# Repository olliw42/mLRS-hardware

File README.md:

# mLRS Hardware #

Repository for some mLRS hardware design files.

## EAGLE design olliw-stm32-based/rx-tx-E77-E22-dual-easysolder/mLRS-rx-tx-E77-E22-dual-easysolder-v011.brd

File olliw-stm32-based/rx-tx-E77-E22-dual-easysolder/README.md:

# mLRS Hardware: Easy-To-Solder Board E77 E22 dual #

For the through-hole parts, Mouser parts numbers are listed in the electric scheme. A list of parts is also available here https://www.mouser.de/ProjectManager/ProjectDetail.aspx?AccessID=b60c19cf3a.

These are of course only suggestions, these and equally suitable parts can be sourced from many places.

The EByte E77-900M22S module is relatively new. It can be ordered from the "EBYTE Official Store" on AliExpress.

The EByte E22-900M22S module is around for some while and can be ordered on AliExpress from several sources (the "EBYTE Official Store" may not be the cheapest offer).

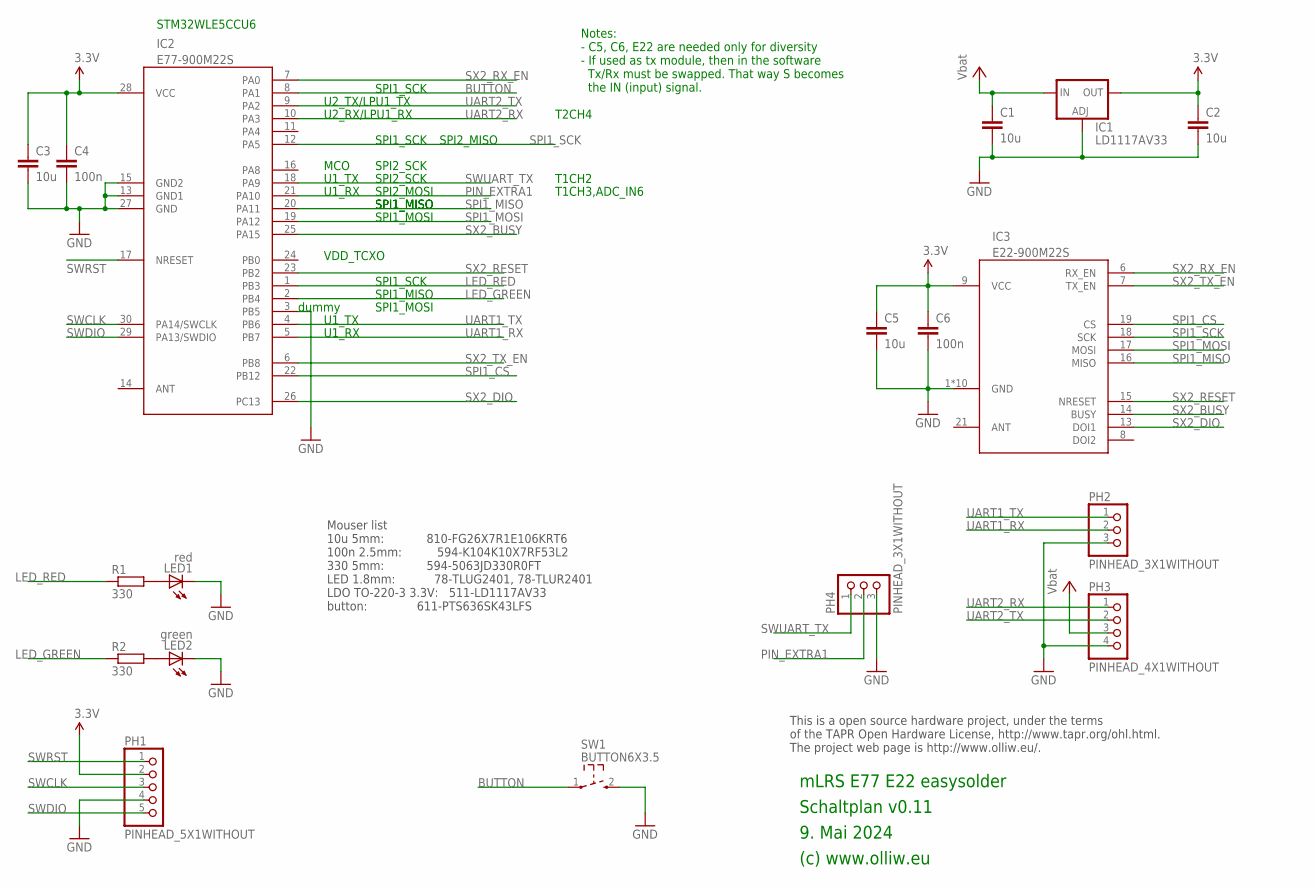
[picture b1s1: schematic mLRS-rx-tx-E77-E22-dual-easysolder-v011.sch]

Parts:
C1, C2: 10u; C050-045X075
C3, C5: 10u; C050-024X044
C4, C6: 100n; C025-024X044
IC1: LD1117AV33; TO220L1
IC2: E77-900M22S
IC3: E22-900M22S
LED1: red; LED1.8MM
LED2: green; LED1.8MM
PH1: PINHEAD_5X1WITHOUT; PINHEAD_5X1_WO
PH2, PH4: PINHEAD_3X1WITHOUT; PINHEAD_3X1_WO
PH3: PINHEAD_4X1WITHOUT; PINHEAD_4X1_WO
R1, R2: 330; R0204/6.25
SW1: BUTTON6X3.5; BUTTON-THT

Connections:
3.3V: C2.1, C3.1, C4.1, C5.1, C6.1, IC1.2 (OUT), IC2.28 (VCC), IC3.9 (VCC), PH1.2
BUTTON: IC2.8 (PA1), SW1.1
GND: C1.2, C2.2, C3.2, C4.2, C5.2, C6.2, IC1.1 (ADJ), IC2.3 (PB5), IC2.13 (GND1), IC2.15 (GND2), IC2.27 (GND), IC3.1 (GND), IC3.2 (GND), IC3.3 (GND), IC3.4 (GND), IC3.5 (GND), IC3.10 (GND), IC3.11 (GND), IC3.12 (GND), IC3.20 (GND), IC3.22 (GND), LED1.K (C), LED2.K (C), PH1.4, PH2.3 (5), PH3.4, PH4.3 (5), SW1.2 (3)
LED_GREEN: IC2.2 (PB4), R2.1
LED_RED: IC2.1 (PB3), R1.1
unnamed: LED1.A, R1.2
unnamed: LED2.A, R2.2
PIN_EXTRA1: IC2.21 (PA10), PH4.2 (3)
SPI1_CS: IC2.22 (PB12), IC3.19 (CS)
SPI1_MISO: IC2.20 (PA11), IC3.16 (MISO)
SPI1_MOSI: IC2.19 (PA12), IC3.17 (MOSI)
SPI1_SCK: IC2.12 (PA5), IC3.18 (SCK)
SWCLK: IC2.30 (PA14/SWCLK), PH1.3
SWDIO: IC2.29 (PA13/SWDIO), PH1.5
SWRST: IC2.17 (NRESET), PH1.1
SWUART_TX: IC2.18 (PA9), PH4.1
SX2_BUSY: IC2.25 (PA15), IC3.14 (BUSY)
SX2_DIO: IC2.26 (PC13), IC3.13 (DOI1)
SX2_RESET: IC2.23 (PB2), IC3.15 (NRESET)
SX2_RX_EN: IC2.7 (PA0), IC3.6 (RX_EN)
SX2_TX_EN: IC2.6 (PB8), IC3.7 (TX_EN)
UART1_RX: IC2.5 (PB7), PH2.2 (3)
UART1_TX: IC2.4 (PB6), PH2.1
UART2_RX: IC2.10 (PA3), PH3.1
UART2_TX: IC2.9 (PA2), PH3.2
VCC: C1.1, IC1.3 (IN), PH3.3

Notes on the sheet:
9. Mai 2024
(c) www.olliw.eu
mLRS E77 E22 easysolder
Schaltplan v0.11
This is a open source hardware project, under the terms of the TAPR Open Hardware License, http://www.tapr.org/ohl.html. The project web page is http://www.olliw.eu/.
SPI1_SCK
SPI1_MISO
SPI1_MOSI
U1_TX
U1_RX
U2_TX/LPU1_TX
U2_RX/LPU1_RX
SPI2_SCK
VDD_TCXO
SPI2_MOSI
SPI2_MISO
STM32WLE5CCU6
T1CH2
T1CH3,ADC_IN6
Mouser list 10u 5mm: 810-FG26X7R1E106KRT6 100n 2.5mm: 594-K104K10X7RF53L2 330 5mm: 594-5063JD330R0FT LED 1.8mm: 78-TLUG2401, 78-TLUR2401 LDO TO-220-3 3.3V: 511-LD1117AV33 button: 611-PTS636SK43LFS
dummy
T2CH4
Notes: - C5, C6, E22 are needed only for diversity - If used as tx module, then in the software Tx/Rx must be swapped. That way S becomes the IN (input) signal.
MCO

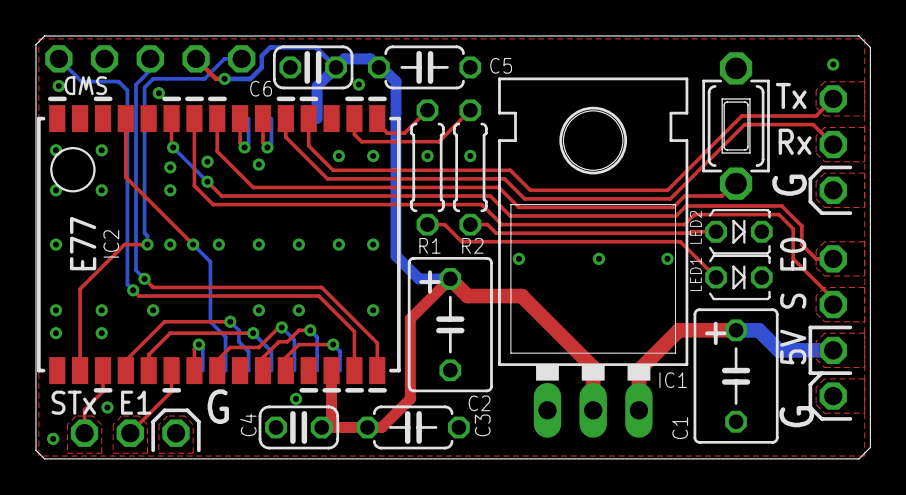
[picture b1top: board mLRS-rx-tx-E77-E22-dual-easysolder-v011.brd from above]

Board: 2 copper layers, 46.4 x 23.5 mm, 18 parts (1 on the bottom side), 26 nets.

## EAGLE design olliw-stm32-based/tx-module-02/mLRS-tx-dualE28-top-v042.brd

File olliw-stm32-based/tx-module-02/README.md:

# ATTENTION #

The v042 designs for the base board, the E22dual board, and the E28dual board are up-to-date.

The v031 dualSx board will not be updated.

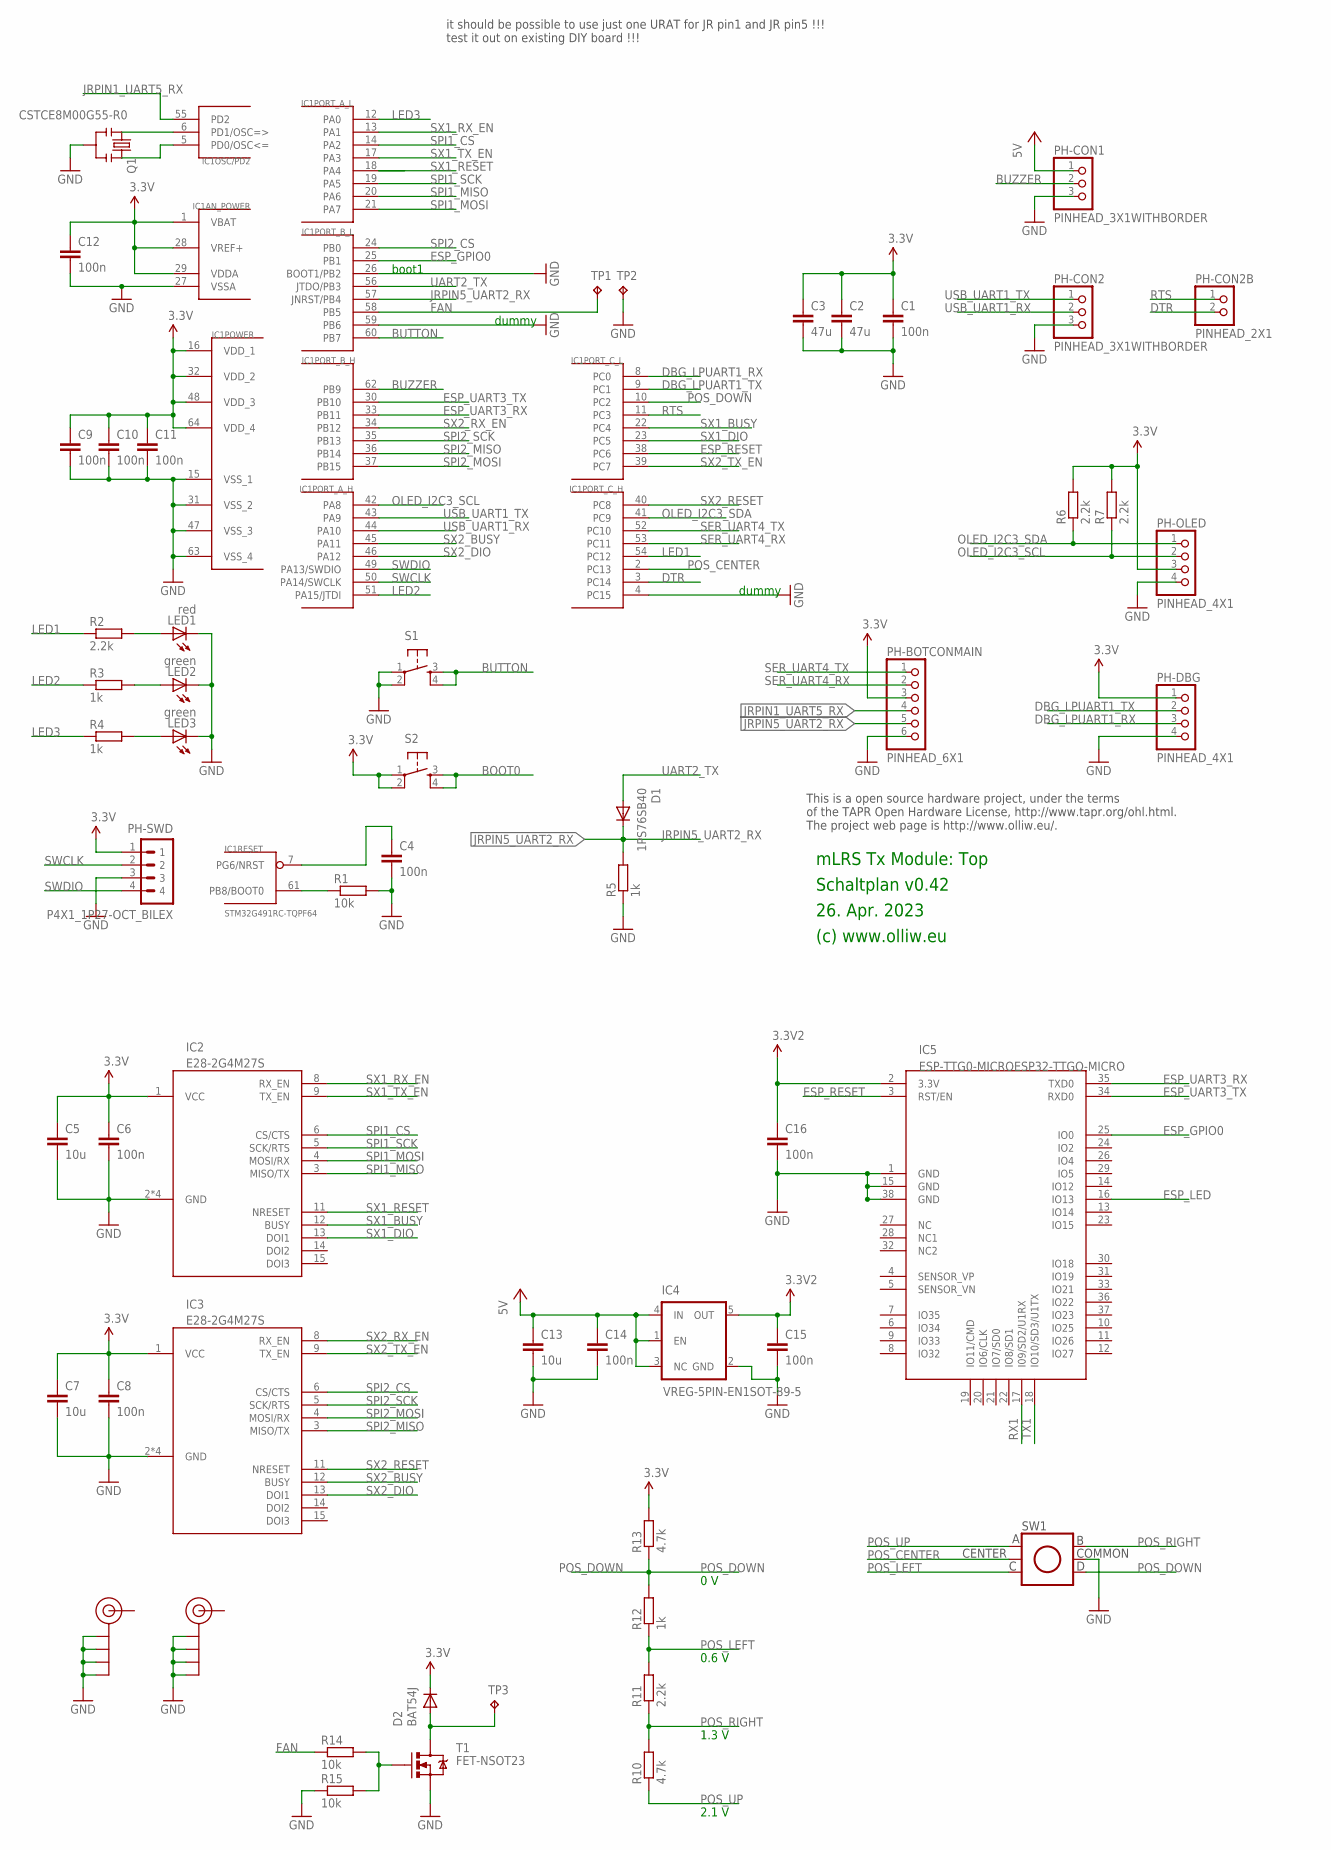
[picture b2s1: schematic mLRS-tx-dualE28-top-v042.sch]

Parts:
C1, C4, C6, C8, C9, C10, C11, C12, C14, C15: 100n; C0402
C2: 47u; C1210
C3: 47u; C1206K
C5, C7, C13: 10u; C0603
C16: 100n; C0603
D1: 1PS76SB40; SOD110-R
D2: BAT54J; SOD110-R
IC1: STM32G491RC-TQPF64; TQFP64
IC2, IC3: E28-2G4M27S; E28-2G4M27
IC4: VREG-5PIN-EN1SOT-89-5; SOT-89-5
IC5: ESP-TTG0-MICROESP32-TTGO-MICRO; ESP32-TTGO-MICRO
LED1: red; CHIPLED_0603
LED2, LED3: green; CHIPLED_0603
PH-BOTCONMAIN: PINHEAD_6X1
PH-CON1, PH-CON2: PINHEAD_3X1WITHBORDER; PINHEAD_3X1
PH-CON2B: PINHEAD_2X1
PH-DBG: PINHEAD_4X1
PH-OLED: PINHEAD_4X1
PH-SWD: P4X1_1P27-OCT_BILEX; 4X1_1P27_OCT_BILEX
Q1: CSTCE8M00G55-R0; RESONATOR-SMD
R1, R14, R15: 10k; R0402
R2, R6, R7, R11: 2.2k; R0402
R3, R4, R5, R12: 1k; R0402
R10, R13: 4.7k; R0402
RF1, RF2: SMA_EDGE; SMA-EDGE
S1, S2: TAC_SWITCHPTH; TACTILE-PTH
SW1: JOYSTICK-5WAY
T1: FET-NSOT23; SOT23
TP1, TP2, TP3: TPB1,27; B1,27

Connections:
2.8V: C15.1, C16.1, IC4.5 (OUT), IC5.2 (3.3V)
3.3V: C1.1, C2.1, C3.1, C5.1, C6.1, C7.1, C8.1, C9.1, C10.1, C11.1, C12.1, D2.C, IC1.1 (VBAT), IC1.16 (VDD_1), IC1.28 (VREF+), IC1.29 (VDDA), IC1.32 (VDD_2), IC1.48 (VDD_3), IC1.64 (VDD_4), IC2.1 (VCC), IC3.1 (VCC), PH-BOTCONMAIN.3, PH-DBG.1, PH-OLED.3, PH-SWD.1, R6.2, R7.2, R13.2, S2.1, S2.2
5V: C13.1, C14.1, IC4.1 (EN), IC4.3 (NC), IC4.4 (IN), PH-CON1.1
BOOT0: IC1.61 (PB8/BOOT0), R1.1, S2.3, S2.4
BUTTON: IC1.60 (PB7), S1.3, S1.4
BUZ-: D2.A, T1.3 (D), TP3.TP
BUZZER: IC1.62 (PB9), PH-CON1.2 (3)
DBG_LPUART1_RX: IC1.8 (PC0), PH-DBG.3
DBG_LPUART1_TX: IC1.9 (PC1), PH-DBG.2
DTR: IC1.3 (PC14), PH-CON2B.2
ESP_GPIO0: IC1.25 (PB1), IC5.25 (IO0)
ESP_LED: IC5.16 (IO13)
ESP_RESET: IC1.38 (PC6), IC5.3 (RST/EN)
ESP_UART3_RX: IC1.33 (PB11), IC5.35 (TXD0)
ESP_UART3_TX: IC1.30 (PB10), IC5.34 (RXD0)
FAN: IC1.58 (PB5), R14.1, TP1.TP
GND: C1.2, C2.2, C3.2, C4.2, C5.2, C6.2, C7.2, C8.2, C9.2, C10.2, C11.2, C12.2, C13.2, C14.2, C15.2, C16.2, IC1.4 (PC15), IC1.15 (VSS_1), IC1.26 (BOOT1/PB2), IC1.27 (VSSA), IC1.31 (VSS_2), IC1.47 (VSS_3), IC1.59 (PB6), IC1.63 (VSS_4), IC2.2 (GND), IC2.7 (GND), IC2.10 (GND), IC2.16 (GND), IC3.2 (GND), IC3.7 (GND), IC3.10 (GND), IC3.16 (GND), IC4.2 (GND), IC5.1 (GND), IC5.15 (GND), IC5.38 (GND), LED1.C, LED2.C, LED3.C, PH-BOTCONMAIN.6, PH-CON1.3 (5), PH-CON2.3 (5), PH-DBG.4, PH-OLED.4, PH-SWD.3, Q1.2, R1.2, R5.1, R15.1, RF1.GND@0 (GND), RF1.GND@1 (GND), RF1.GND@2 (GND), RF1.GND@3 (GND), RF2.GND@0 (GND), RF2.GND@1 (GND), RF2.GND@2 (GND), RF2.GND@3 (GND), S1.1, S1.2, SW1.5 (COMMON), T1.2 (S), TP2.TP
JRPIN1_UART5_RX: IC1.55 (PD2), PH-BOTCONMAIN.4
JRPIN5_UART2_RX: D1.C, IC1.57 (JNRST/PB4), PH-BOTCONMAIN.5, R5.2
LED1: IC1.54 (PC12), R2.1
LED2: IC1.51 (PA15/JTDI), R3.1
LED3: IC1.12 (PA0), R4.1
unnamed: R14.2, R15.2, T1.1 (G)
unnamed: LED1.A, R2.2
unnamed: C4.1, IC1.7 (PG6/NRST)
unnamed: LED2.A, R3.2
unnamed: LED3.A, R4.2
unnamed: IC1.5 (PD0/OSC<=), Q1.3
unnamed: IC1.6 (PD1/OSC=>), Q1.1
OLED_I2C3_SCL: IC1.42 (PA8), PH-OLED.2, R7.1
OLED_I2C3_SDA: IC1.41 (PC9), PH-OLED.1, R6.1
POS_CENTER: IC1.2 (PC13), SW1.2 (CENTER)
POS_DOWN: IC1.10 (PC2), R12.2, R13.1, SW1.6 (D)
POS_LEFT: R11.2, R12.1, SW1.3 (C)
POS_RIGHT: R10.2, R11.1, SW1.4 (B)
POS_UP: R10.1, SW1.1 (A)
RTS: IC1.11 (PC3), PH-CON2B.1
RX1: IC5.17 (I09/SD2/U1RX)
SER_UART4_RX: IC1.53 (PC11), PH-BOTCONMAIN.2
SER_UART4_TX: IC1.52 (PC10), PH-BOTCONMAIN.1
SPI1_CS: IC1.14 (PA2), IC2.6 (CS/CTS)
SPI1_MISO: IC1.20 (PA6), IC2.3 (MISO/TX)
SPI1_MOSI: IC1.21 (PA7), IC2.4 (MOSI/RX)
SPI1_SCK: IC1.19 (PA5), IC2.5 (SCK/RTS)
SPI2_CS: IC1.24 (PB0), IC3.6 (CS/CTS)
SPI2_MISO: IC1.36 (PB14), IC3.3 (MISO/TX)
SPI2_MOSI: IC1.37 (PB15), IC3.4 (MOSI/RX)
SPI2_SCK: IC1.35 (PB13), IC3.5 (SCK/RTS)
SWCLK: IC1.50 (PA14/SWCLK), PH-SWD.2
SWDIO: IC1.49 (PA13/SWDIO), PH-SWD.4
SX1_BUSY: IC1.22 (PC4), IC2.12 (BUSY)
SX1_DIO: IC1.23 (PC5), IC2.13 (DOI1)
SX1_RESET: IC1.18 (PA4), IC2.11 (NRESET)
SX1_RX_EN: IC1.13 (PA1), IC2.8 (RX_EN)
SX1_TX_EN: IC1.17 (PA3), IC2.9 (TX_EN)
SX2_BUSY: IC1.45 (PA11), IC3.12 (BUSY)
SX2_DIO: IC1.46 (PA12), IC3.13 (DOI1)
SX2_RESET: IC1.40 (PC8), IC3.11 (NRESET)
SX2_RX_EN: IC1.34 (PB12), IC3.8 (RX_EN)
SX2_TX_EN: IC1.39 (PC7), IC3.9 (TX_EN)
TX1: IC5.18 (IO10/SD3/U1TX)
UART2_TX: D1.A, IC1.56 (JTDO/PB3)
USB_UART1_RX: IC1.44 (PA10), PH-CON2.2 (3)
USB_UART1_TX: IC1.43 (PA9), PH-CON2.1

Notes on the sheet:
26. Apr. 2023
(c) www.olliw.eu
mLRS Tx Module: Top
Schaltplan v0.42
This is a open source hardware project, under the terms of the TAPR Open Hardware License, http://www.tapr.org/ohl.html. The project web page is http://www.olliw.eu/.
boot1
it should be possible to use just one URAT for JR pin1 and JR pin5 !!! test it out on existing DIY board !!!
0 V
0.6 V
1.3 V
2.1 V
dummy

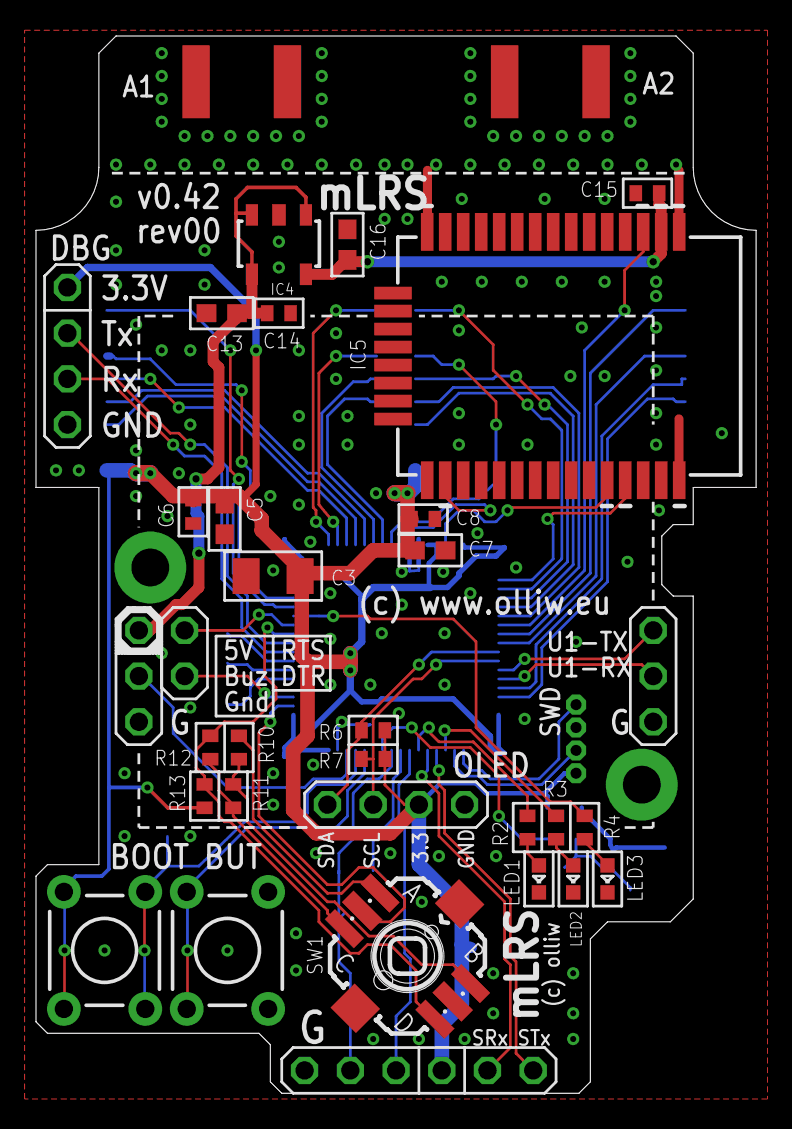
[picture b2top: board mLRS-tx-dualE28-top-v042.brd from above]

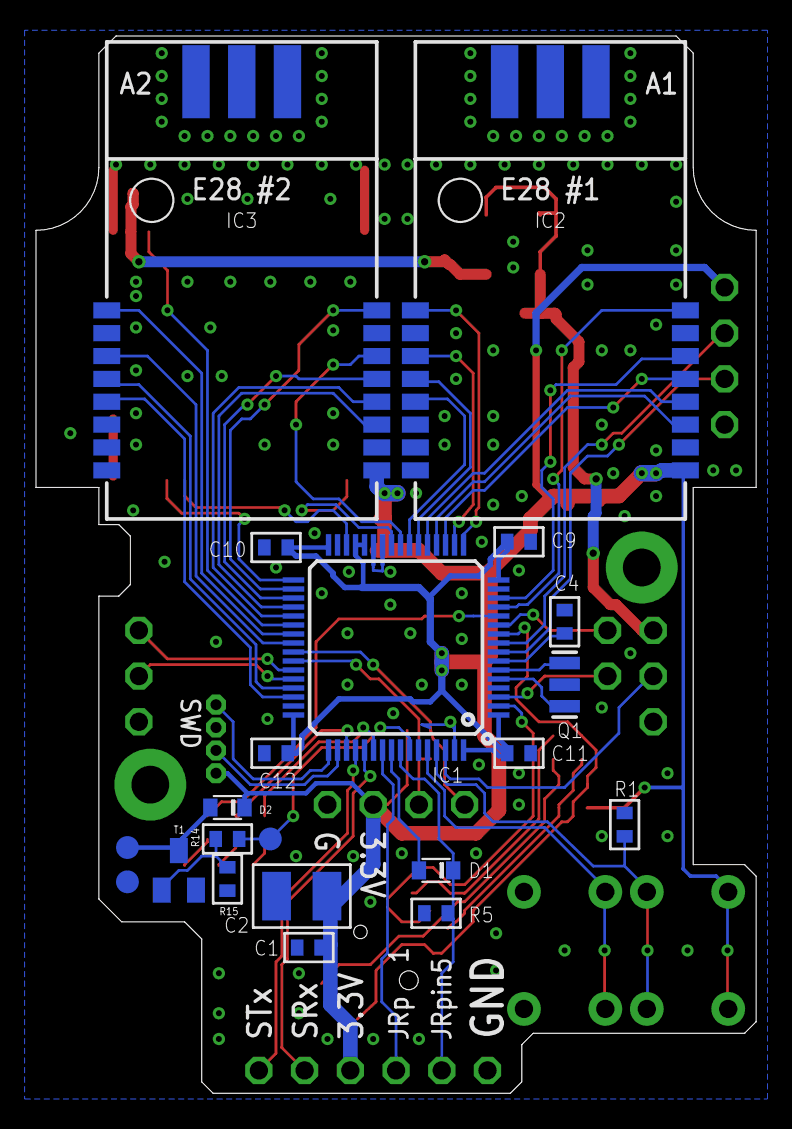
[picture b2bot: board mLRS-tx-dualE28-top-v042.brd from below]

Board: 2 copper layers, 40.0 x 58.7 mm, 56 parts (23 on the bottom side), 61 nets.

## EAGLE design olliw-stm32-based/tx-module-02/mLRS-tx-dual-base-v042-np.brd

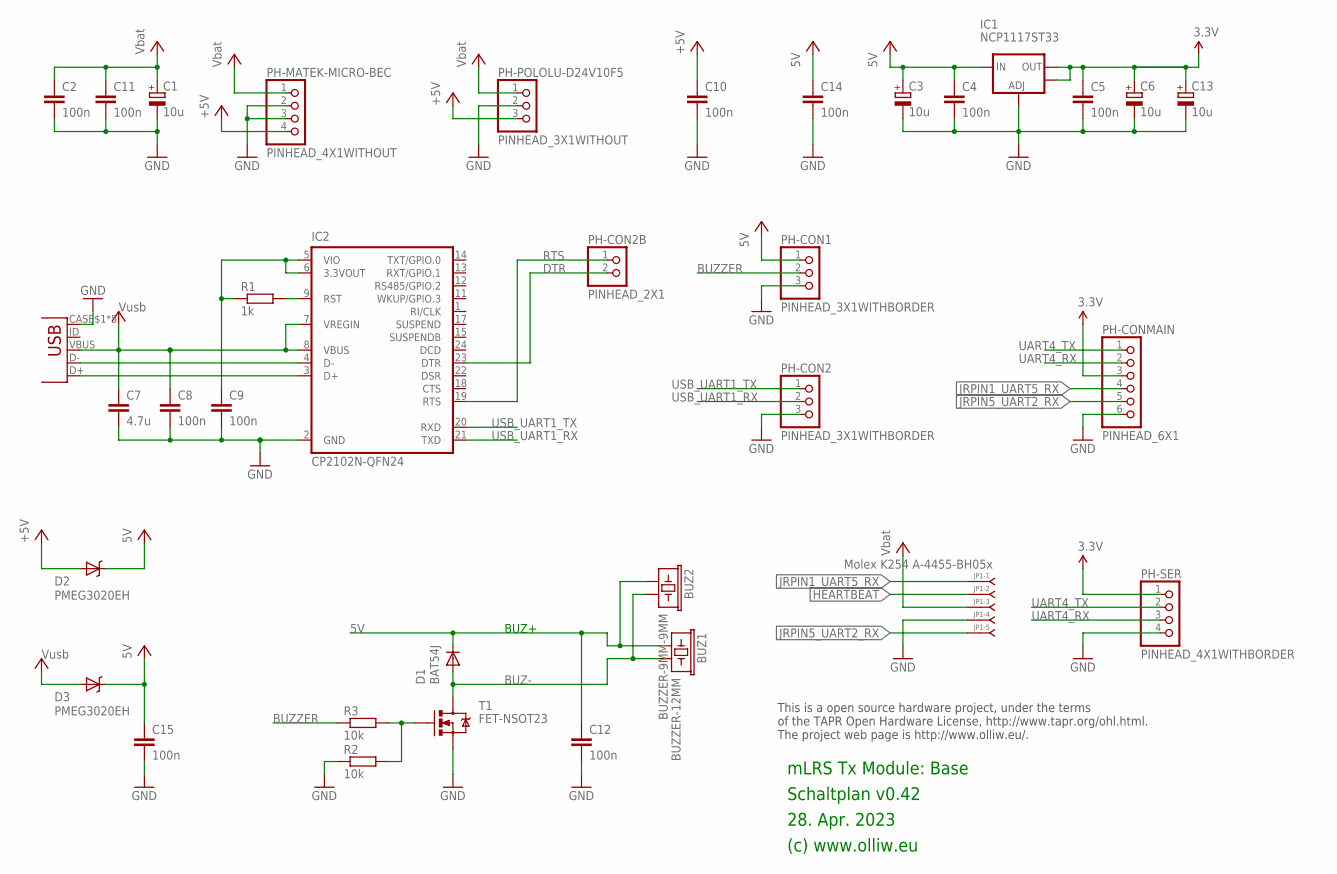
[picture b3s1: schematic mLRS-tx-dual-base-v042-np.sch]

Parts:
BUZ1: BUZZER-12MM
BUZ2: BUZZER-9MM-9MM; BUZZER-9MM
C1, C3, C6, C13: 10u; SMC_A
C2, C4, C5, C10, C11, C12, C14, C15: 100n; C0603
C7: 4.7u; C0603
C8, C9: 100n; C0402
D1: BAT54J; SOD110-R
D2, D3: PMEG3020EH; SOD123W-DIODE
IC1: NCP1117ST33; SOT223
IC2: CP2102N-QFN24; QFN24-CP2102N
JP1: Molex K254 A-4455-BH05x; 4455-B05
PH-CON1, PH-CON2: PINHEAD_3X1WITHBORDER; PINHEAD_3X1
PH-CON2B: PINHEAD_2X1
PH-CONMAIN: PINHEAD_6X1
PH-MATEK-MICRO-BEC: PINHEAD_4X1WITHOUT; PINHEAD_4X1_WO
PH-POLOLU-D24V10F5: PINHEAD_3X1WITHOUT; PINHEAD_3X1_WO
PH-SER: PINHEAD_4X1WITHBORDER; PINHEAD_4X1
R1: 1k; R0402
R2, R3: 10k; R0402
T1: FET-NSOT23; SOT23
USB1: USB-MICROB-UP-NONPLATED

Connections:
3.3V: C5.1, C6.+, C13.+, IC1.2 (OUT), IC1.4 (OUT), PH-CONMAIN.3, PH-SER.1
3.3V-CP2102: C9.1, IC2.5 (VIO), IC2.6 (3.3VOUT), R1.1
5V: BUZ1.+ (1), BUZ2.+ (1), C3.+, C4.1, C12.1, C14.1, C15.1, D1.C, D2.C, D3.C, IC1.3 (IN), PH-CON1.1
+5V: C10.1, D2.A, PH-MATEK-MICRO-BEC.4, PH-POLOLU-D24V10F5.3 (5)
BUZ-: BUZ1.- (2), BUZ2.- (2), D1.A, T1.3 (D)
BUZZER: PH-CON1.2 (3), R3.1
DTR: IC2.23 (DTR), PH-CON2B.2
GND: C1.-, C2.2, C3.-, C4.2, C5.2, C6.-, C7.2, C8.2, C9.2, C10.2, C11.2, C12.2, C13.-, C14.2, C15.2, IC1.1 (ADJ), IC2.2 (GND), JP1.4, PH-CON1.3 (5), PH-CON2.3 (5), PH-CONMAIN.6, PH-MATEK-MICRO-BEC.2, PH-MATEK-MICRO-BEC.3, PH-POLOLU-D24V10F5.2 (3), PH-SER.4, R2.1, T1.2 (S), USB1.CASE$1 (GND), USB1.CASE$2 (GND), USB1.CASE$3 (GND), USB1.CASE$4 (GND), USB1.GND
HEARTBEAT: JP1.2
JRPIN1_UART5_RX: JP1.1, PH-CONMAIN.4
JRPIN5_UART2_RX: JP1.5, PH-CONMAIN.5
unnamed: IC2.4 (D-), USB1.D-
unnamed: R2.2, R3.2, T1.1 (G)
unnamed: IC2.3 (D+), USB1.D+
unnamed: IC2.9 (RST), R1.2
RTS: IC2.19 (RTS), PH-CON2B.1
UART4_RX: PH-CONMAIN.2, PH-SER.3
UART4_TX: PH-CONMAIN.1, PH-SER.2
USB_UART1_RX: IC2.21 (TXD), PH-CON2.2 (3)
USB_UART1_TX: IC2.20 (RXD), PH-CON2.1
VBAT: C1.+, C2.1, C11.1, JP1.3, PH-MATEK-MICRO-BEC.1, PH-POLOLU-D24V10F5.1
VUSB: C7.1, C8.1, D3.A, IC2.7 (VREGIN), IC2.8 (VBUS), USB1.VBUS

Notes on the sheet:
28. Apr. 2023
(c) www.olliw.eu
mLRS Tx Module: Base
Schaltplan v0.42
This is a open source hardware project, under the terms of the TAPR Open Hardware License, http://www.tapr.org/ohl.html. The project web page is http://www.olliw.eu/.
BUZ+

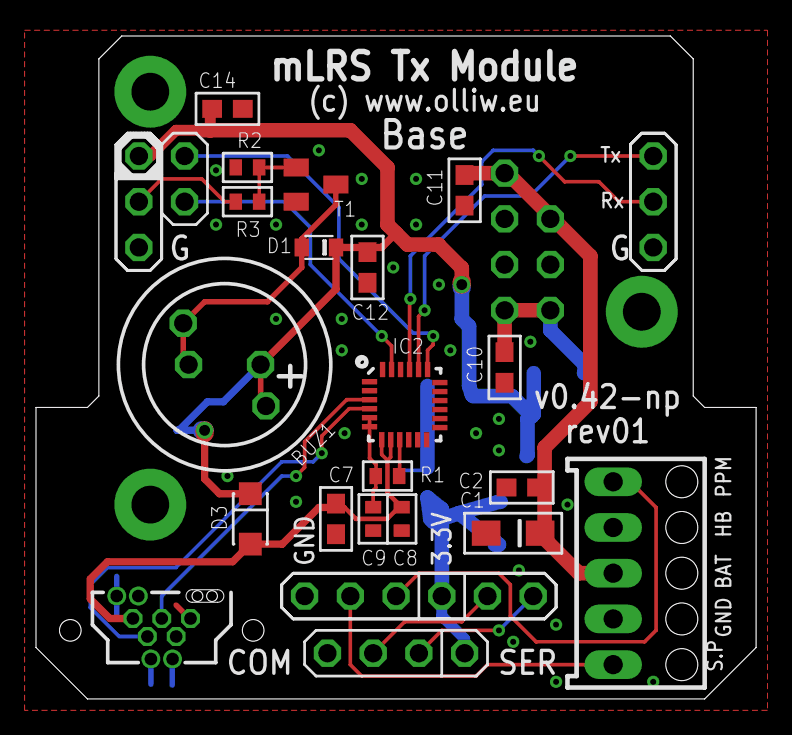
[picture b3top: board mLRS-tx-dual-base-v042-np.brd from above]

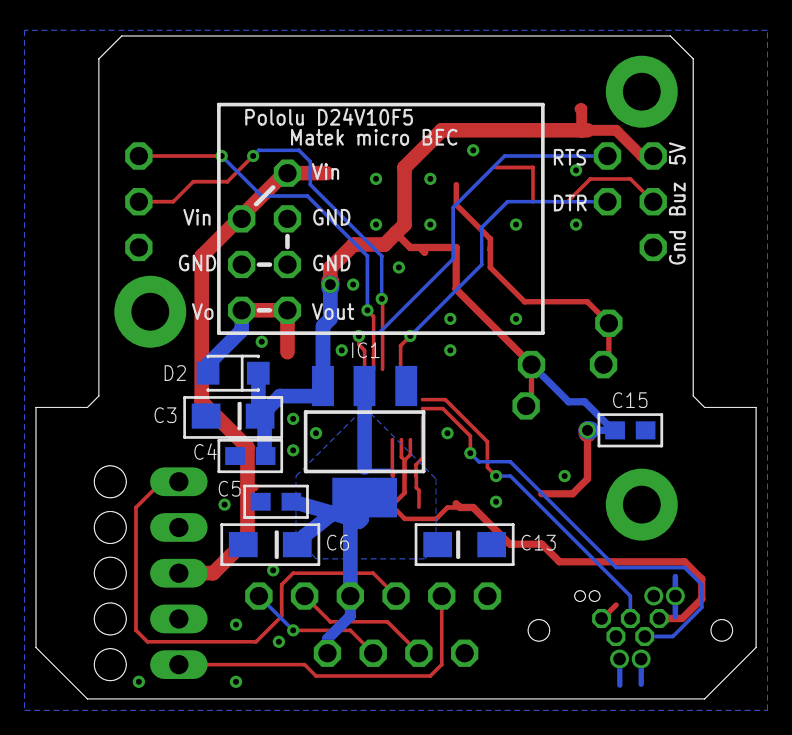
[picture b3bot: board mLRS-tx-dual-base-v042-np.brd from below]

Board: 2 copper layers, 40.0 x 36.8 mm, 35 parts (8 on the bottom side), 21 nets.

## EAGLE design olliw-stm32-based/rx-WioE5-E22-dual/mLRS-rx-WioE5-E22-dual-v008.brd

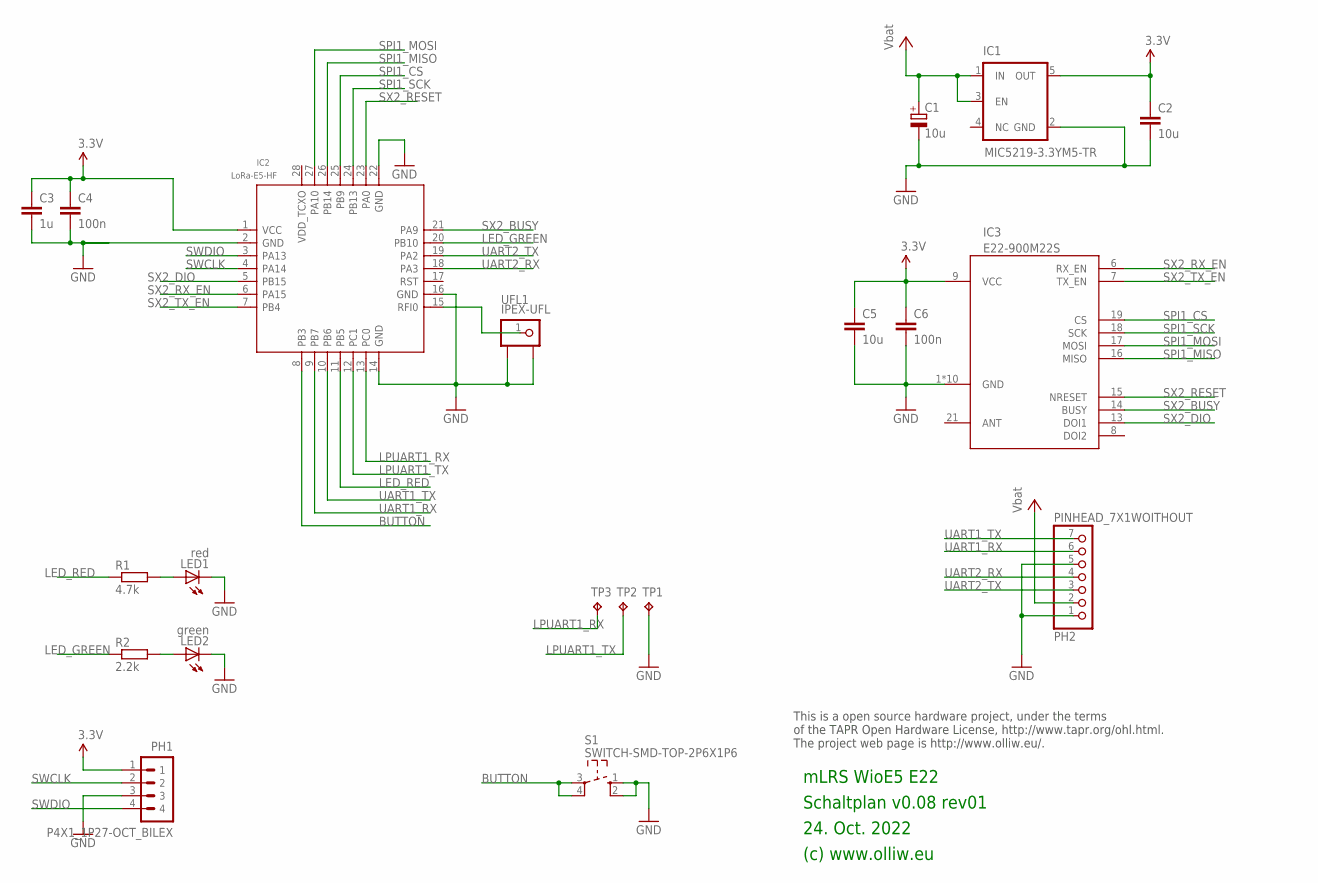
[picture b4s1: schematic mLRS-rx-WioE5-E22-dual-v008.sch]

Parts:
C1: 10u; SMC_A
C2: 10u; C0805
C3: 1u; C0603K
C4, C6: 100n; C0402
C5: 10u; C0805K
IC1: MIC5219-3.3YM5-TR; SOT23-5
IC2: LoRa-E5-HF; MOUDLE28P-1.25-12X12X2.5MM
IC3: E22-900M22S
LED1: red; CHIPLED_0603
LED2: green; CHIPLED_0603
PH1: P4X1_1P27-OCT_BILEX; 4X1_1P27_OCT_BILEX
PH2: PINHEAD_7X1WOITHOUT; PINHEAD_7X1_WO
R1: 4.7k; R0402
R2: 2.2k; R0402
S1: SWITCH-SMD-TOP-2P6X1P6; TACTILE-SWITCH-SMD-TOP-2P6X1X6
TP1, TP2, TP3: TPB1,27; B1,27
UFL1: IPEX-UFL; IPEX-UFL-SMD

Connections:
3.3V: C2.1, C3.1, C4.1, C5.1, C6.1, IC1.5 (OUT), IC2.1 (VCC), IC3.9 (VCC), PH1.1
BUTTON: IC2.8 (PB3), S1.3, S1.4
GND: C1.-, C2.2, C3.2, C4.2, C5.2, C6.2, IC1.2 (GND), IC2.2 (GND), IC2.14 (GND), IC2.16 (GND), IC2.22 (GND), IC3.1 (GND), IC3.2 (GND), IC3.3 (GND), IC3.4 (GND), IC3.5 (GND), IC3.10 (GND), IC3.11 (GND), IC3.12 (GND), IC3.20 (GND), IC3.22 (GND), LED1.C, LED2.C, PH1.3, PH2.1, PH2.5, S1.1, S1.2, TP1.TP, UFL1.2, UFL1.3
LED_GREEN: IC2.20 (PB10), R2.1
LED_RED: IC2.11 (PB5), R1.1
LPUART1_RX: IC2.13 (PC0), TP3.TP
LPUART1_TX: IC2.12 (PC1), TP2.TP
unnamed: IC2.15 (RFI0), UFL1.1
unnamed: LED1.A, R1.2
unnamed: LED2.A, R2.2
SPI1_CS: IC2.25 (PB9), IC3.19 (CS)
SPI1_MISO: IC2.26 (PB14), IC3.16 (MISO)
SPI1_MOSI: IC2.27 (PA10), IC3.17 (MOSI)
SPI1_SCK: IC2.24 (PB13), IC3.18 (SCK)
SWCLK: IC2.4 (PA14), PH1.2
SWDIO: IC2.3 (PA13), PH1.4
SX2_BUSY: IC2.21 (PA9), IC3.14 (BUSY)
SX2_DIO: IC2.5 (PB15), IC3.13 (DOI1)
SX2_RESET: IC2.23 (PA0), IC3.15 (NRESET)
SX2_RX_EN: IC2.6 (PA15), IC3.6 (RX_EN)
SX2_TX_EN: IC2.7 (PB4), IC3.7 (TX_EN)
UART1_RX: IC2.9 (PB7), PH2.6
UART1_TX: IC2.10 (PB6), PH2.7
UART2_RX: IC2.18 (PA3), PH2.4
UART2_TX: IC2.19 (PA2), PH2.3
VCC: C1.+, IC1.1 (IN), IC1.3 (EN), PH2.2

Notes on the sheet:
24. Oct. 2022
(c) www.olliw.eu
mLRS WioE5 E22
Schaltplan v0.08 rev01
This is a open source hardware project, under the terms of the TAPR Open Hardware License, http://www.tapr.org/ohl.html. The project web page is http://www.olliw.eu/.

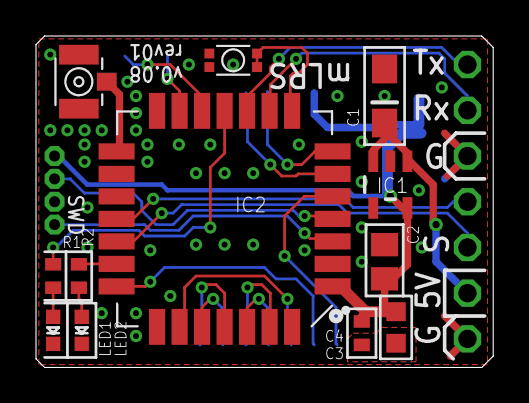
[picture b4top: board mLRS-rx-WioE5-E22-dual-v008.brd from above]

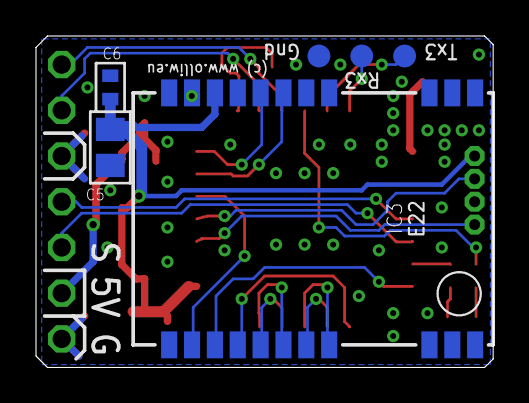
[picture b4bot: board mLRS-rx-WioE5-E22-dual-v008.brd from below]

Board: 2 copper layers, 25.4 x 18.4 mm, 20 parts (6 on the bottom side), 26 nets.

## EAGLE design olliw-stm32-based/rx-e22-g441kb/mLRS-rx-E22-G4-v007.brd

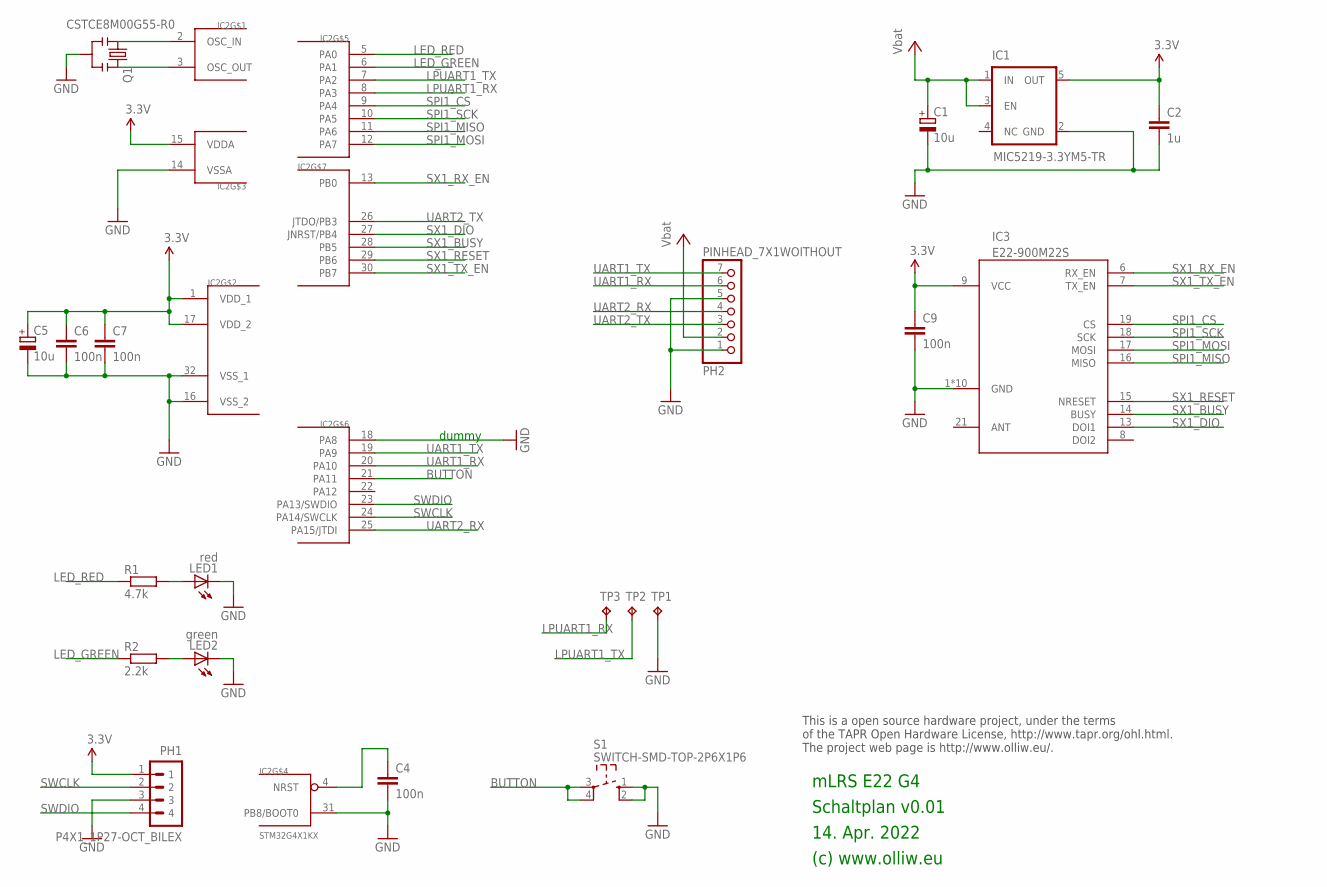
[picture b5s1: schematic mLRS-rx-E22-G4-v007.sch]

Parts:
C1, C5: 10u; SMC_A
C2: 1u; C0603K
C4, C6, C7, C9: 100n; C0402
IC1: MIC5219-3.3YM5-TR; SOT23-5
IC2: STM32G4X1KX; UFQFPN32
IC3: E22-900M22S
LED1: red; CHIPLED_0603
LED2: green; CHIPLED_0603
PH1: P4X1_1P27-OCT_BILEX; 4X1_1P27_OCT_BILEX
PH2: PINHEAD_7X1WOITHOUT; PINHEAD_7X1_WO
Q1: CSTCE8M00G55-R0; RESONATOR-SMD
R1: 4.7k; R0402
R2: 2.2k; R0402
S1: SWITCH-SMD-TOP-2P6X1P6; TACTILE-SWITCH-SMD-TOP-2P6X1X6
TP1, TP2, TP3: TPB1,27; B1,27

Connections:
3.3V: C2.1, C5.+, C6.1, C7.1, C9.1, IC1.5 (OUT), IC2.1 (VDD_1), IC2.15 (VDDA), IC2.17 (VDD_2), IC3.9 (VCC), PH1.1
BUTTON: IC2.21 (PA11), S1.3, S1.4
GND: C1.-, C2.2, C4.2, C5.-, C6.2, C7.2, C9.2, IC1.2 (GND), IC2.14 (VSSA), IC2.16 (VSS_2), IC2.18 (PA8), IC2.31 (PB8/BOOT0), IC2.32 (VSS_1), IC3.1 (GND), IC3.2 (GND), IC3.3 (GND), IC3.4 (GND), IC3.5 (GND), IC3.10 (GND), IC3.11 (GND), IC3.12 (GND), IC3.20 (GND), IC3.22 (GND), LED1.C, LED2.C, PH1.3, PH2.1, PH2.5, Q1.2, S1.1, S1.2, TP1.TP
LED_GREEN: IC2.6 (PA1), R2.1
LED_RED: IC2.5 (PA0), R1.1
LPUART1_RX: IC2.8 (PA3), TP3.TP
LPUART1_TX: IC2.7 (PA2), TP2.TP
unnamed: C4.1, IC2.4 (NRST)
unnamed: IC2.3 (OSC_OUT), Q1.3
unnamed: IC2.2 (OSC_IN), Q1.1
unnamed: LED1.A, R1.2
unnamed: LED2.A, R2.2
SPI1_CS: IC2.9 (PA4), IC3.19 (CS)
SPI1_MISO: IC2.11 (PA6), IC3.16 (MISO)
SPI1_MOSI: IC2.12 (PA7), IC3.17 (MOSI)
SPI1_SCK: IC2.10 (PA5), IC3.18 (SCK)
SWCLK: IC2.24 (PA14/SWCLK), PH1.2
SWDIO: IC2.23 (PA13/SWDIO), PH1.4
SX1_BUSY: IC2.28 (PB5), IC3.14 (BUSY)
SX1_DIO: IC2.27 (JNRST/PB4), IC3.13 (DOI1)
SX1_RESET: IC2.29 (PB6), IC3.15 (NRESET)
SX1_RX_EN: IC2.13 (PB0), IC3.6 (RX_EN)
SX1_TX_EN: IC2.30 (PB7), IC3.7 (TX_EN)
UART1_RX: IC2.20 (PA10), PH2.6
UART1_TX: IC2.19 (PA9), PH2.7
UART2_RX: IC2.25 (PA15/JTDI), PH2.4
UART2_TX: IC2.26 (JTDO/PB3), PH2.3
VCC: C1.+, IC1.1 (IN), IC1.3 (EN), PH2.2

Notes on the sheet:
14. Apr. 2022
(c) www.olliw.eu
mLRS E22 G4
Schaltplan v0.01
This is a open source hardware project, under the terms of the TAPR Open Hardware License, http://www.tapr.org/ohl.html. The project web page is http://www.olliw.eu/.
dummy

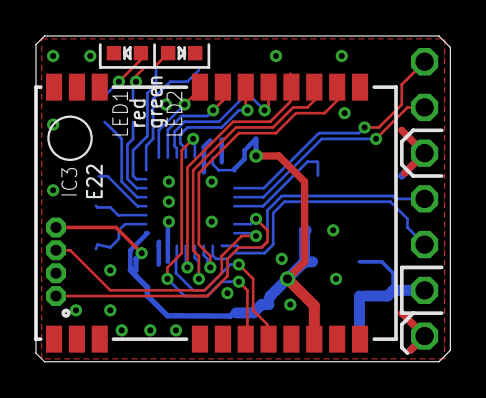
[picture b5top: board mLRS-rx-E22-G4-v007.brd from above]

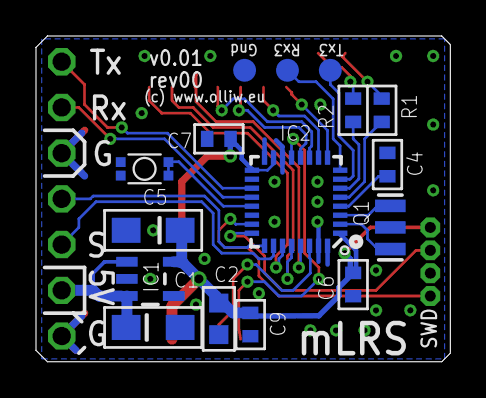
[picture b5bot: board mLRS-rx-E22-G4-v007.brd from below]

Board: 2 copper layers, 23.0 x 18.1 mm, 21 parts (16 on the bottom side), 28 nets.

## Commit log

2021-12-19 mLRS-rx
2021-12-19 mLRS tx jr bay module
2021-12-24 tidy
2021-12-26 add E28 board 001
2022-01-08 rx board01 v014 rev01
2022-01-09 rx board01 v014 rev02
2022-05-06 add rx tx diy dual-E28 board02 f103cb
2022-05-18 rx tx module02 dualE28 F103CB v011, buzzer pad added
2022-05-20 tx module 02 g491re v0.31, dual E28 and dual SX
2022-05-20 rx diy E28 g441kb v0.07
2022-09-02 rename tx dual base module, as it is the same for all three tops, E28, Sx, and E22
2022-09-02 add E22 diy modules
2022-09-02 add scheme, top, bot .png graphics
2023-02-05 add rx WioE5 E22 dual module
2023-02-05 add more top,bot,bot-r,scheme pictures
2023-02-24 add rx-tx E77 E22 dual easysolder module
2023-02-24 RX Gerbers Added
2023-02-24 Tx gerbers added
2023-02-24 Gerbers Added
    * RX Gerbers Added
    * Tx gerbers added
2023-02-25 add parts info for easysolder module
2023-02-25 easysolder board, update readme
2023-04-23 add WARNING that tx module02 v0.3x designs are legacy
2023-04-30 tx-module02, E22dual and base boards updated to v042 designs
2023-06-15 tx-module02, E28dual board updated to v042 design
2023-08-30 rx board01 add png's
2023-09-02 add diy E77 E28 easysolder
2023-09-02 add gerbers
2023-09-02 diy E77 E28 dual band, add gerbers
2024-05-01 E77 easy solder, dual and dualband, v0.10
2024-05-08 dual band gerbers
2024-05-09 E77 easy solder , dual/diversity and dual band, v0.11
2024-05-09 e77 gerbers
2024-05-09 E77 easysolder boards, add gerber files

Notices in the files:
parts and their libraries:
Licensing: CC v3.0 Share-Alike You are welcome to use this library for commercial purposes.
con-molex-kk: Copyright (C) 2010, Bob Starr
